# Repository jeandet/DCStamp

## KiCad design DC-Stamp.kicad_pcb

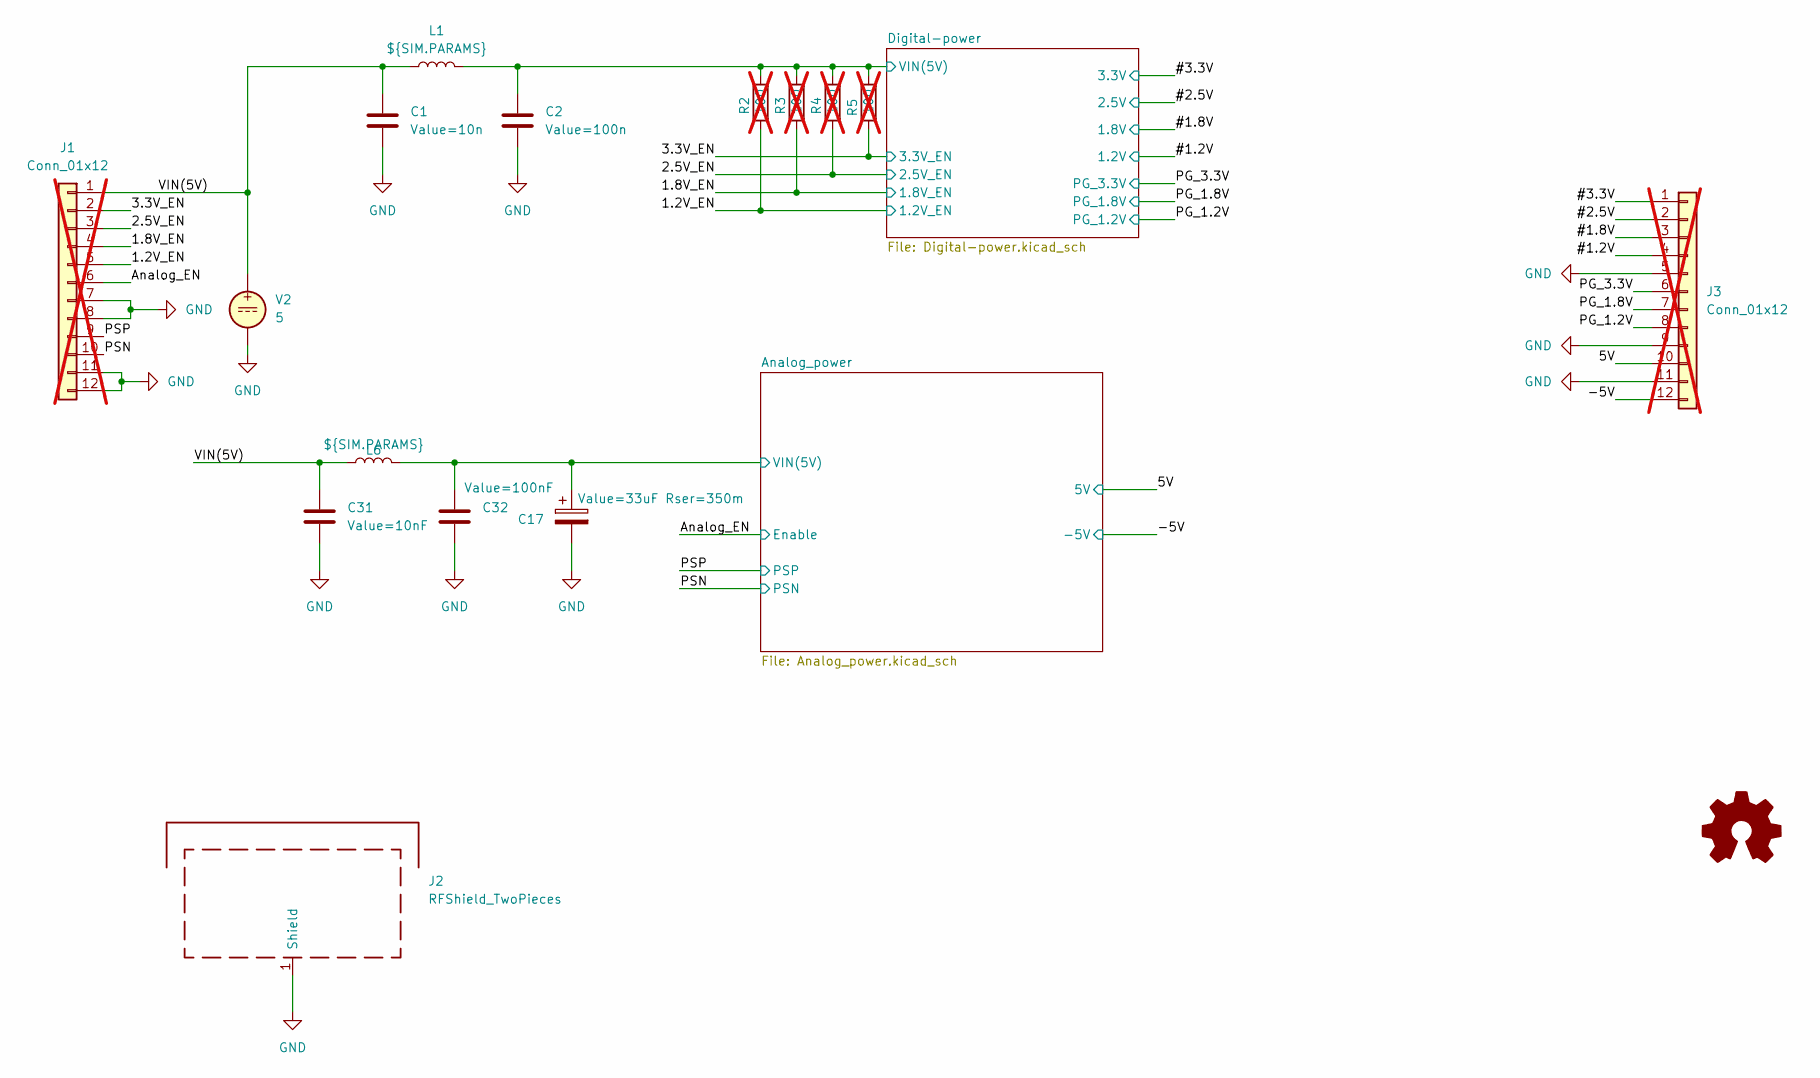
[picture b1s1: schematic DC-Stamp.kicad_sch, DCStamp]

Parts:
C1: Value=10n; C_0603_1608Metric_Pad1.08x0.95mm_HandSolder
C2: Value=100n; C_0603_1608Metric_Pad1.08x0.95mm_HandSolder
C17: Value=33uF Rser=350m; CP_EIA-3528-21_Kemet-B_Pad1.50x2.35mm_HandSolder
C31: Value=10nF; C_0603_1608Metric_Pad1.08x0.95mm_HandSolder
C32: Value=100nF; C_0603_1608Metric_Pad1.08x0.95mm_HandSolder
J1, J3: Conn_01x12; PinHeader_1x12_P2.54mm_Vertical; not fitted
J2: RFShield_TwoPieces; Laird_Technologies_BMI-S-104_32.00x32.00mm
L1, L6: ${SIM.PARAMS}; L_1210_3225Metric_Pad1.42x2.65mm_HandSolder
R2, R3, R4, R5: 100; R_0402_1005Metric_Pad0.72x0.64mm_HandSolder; not fitted
V2: 5
logo1: Logo_Open_Hardware_Small; KiCad-Logo2_5mm_SilkScreen

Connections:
/1.2V_EN: J1.5, R2.2; also elsewhere on the board
/1.8V_EN: J1.4, R3.2; also elsewhere on the board
/2.5V_EN: J1.3, R4.2; also elsewhere on the board
/3.3V_EN: J1.2, R5.2; also elsewhere on the board
/5V: J3.10; also elsewhere on the board
/#1.2V: J3.4; also elsewhere on the board
/#1.8V: J3.3; also elsewhere on the board
/#2.5V: J3.2; also elsewhere on the board
/#3.3V: J3.1; also elsewhere on the board
/-5V: J3.12; also elsewhere on the board
/Analog_EN: J1.6; also elsewhere on the board
/Analog_power/VIN(5V): C17.1, C32.1, L6.2; also elsewhere on the board
/Digital-power/VIN(5V): C2.1, L1.2, R2.1, R3.1, R4.1, R5.1; also elsewhere on the board
/PG_1.2V: J3.8; also elsewhere on the board
/PG_1.8V: J3.7; also elsewhere on the board
/PG_3.3V: J3.6; also elsewhere on the board
/PSN: J1.10; also elsewhere on the board
/PSP: J1.9; also elsewhere on the board
/VIN(5V): C1.1, C31.1, J1.1, L1.1, L6.1, V2.1
GND: C1.2, C2.2, C17.2, C31.2, C32.2, J1.7, J1.8, J1.11, J1.12, J2.1 (Shield), J3.5, J3.9, J3.11, V2.2; also elsewhere on the board

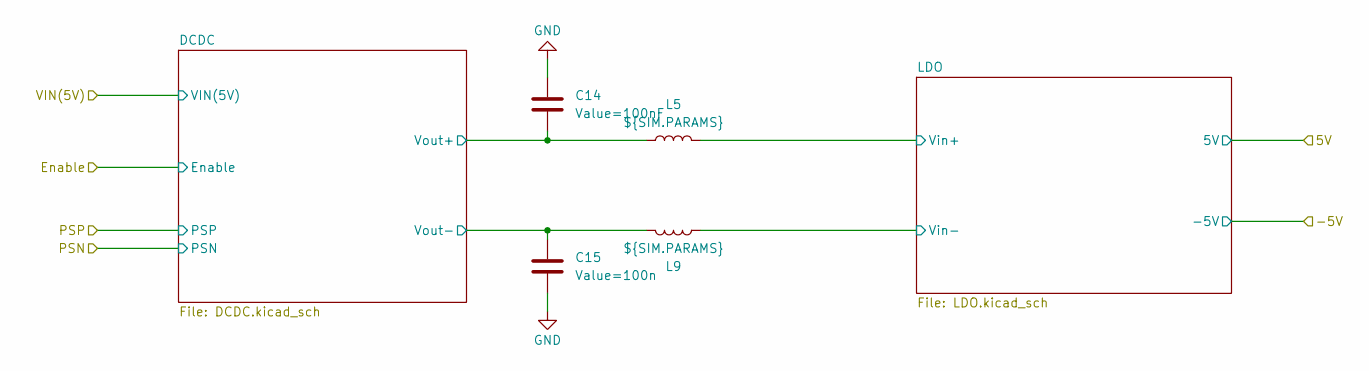
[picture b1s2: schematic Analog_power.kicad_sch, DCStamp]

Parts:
C14: Value=100nF; C_0603_1608Metric_Pad1.08x0.95mm_HandSolder
C15: Value=100n; C_0603_1608Metric_Pad1.08x0.95mm_HandSolder
L5, L9: ${SIM.PARAMS}; L_1210_3225Metric_Pad1.42x2.65mm_HandSolder

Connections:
/Analog_power/DCDC/Vout+: C14.2, L5.1; also elsewhere on the board
/Analog_power/DCDC/Vout-: C15.1, L9.1; also elsewhere on the board
/Analog_power/LDO/Vin+: L5.2; also elsewhere on the board
/Analog_power/LDO/Vin-: L9.2; also elsewhere on the board
GND: C14.1, C15.2; also elsewhere on the board

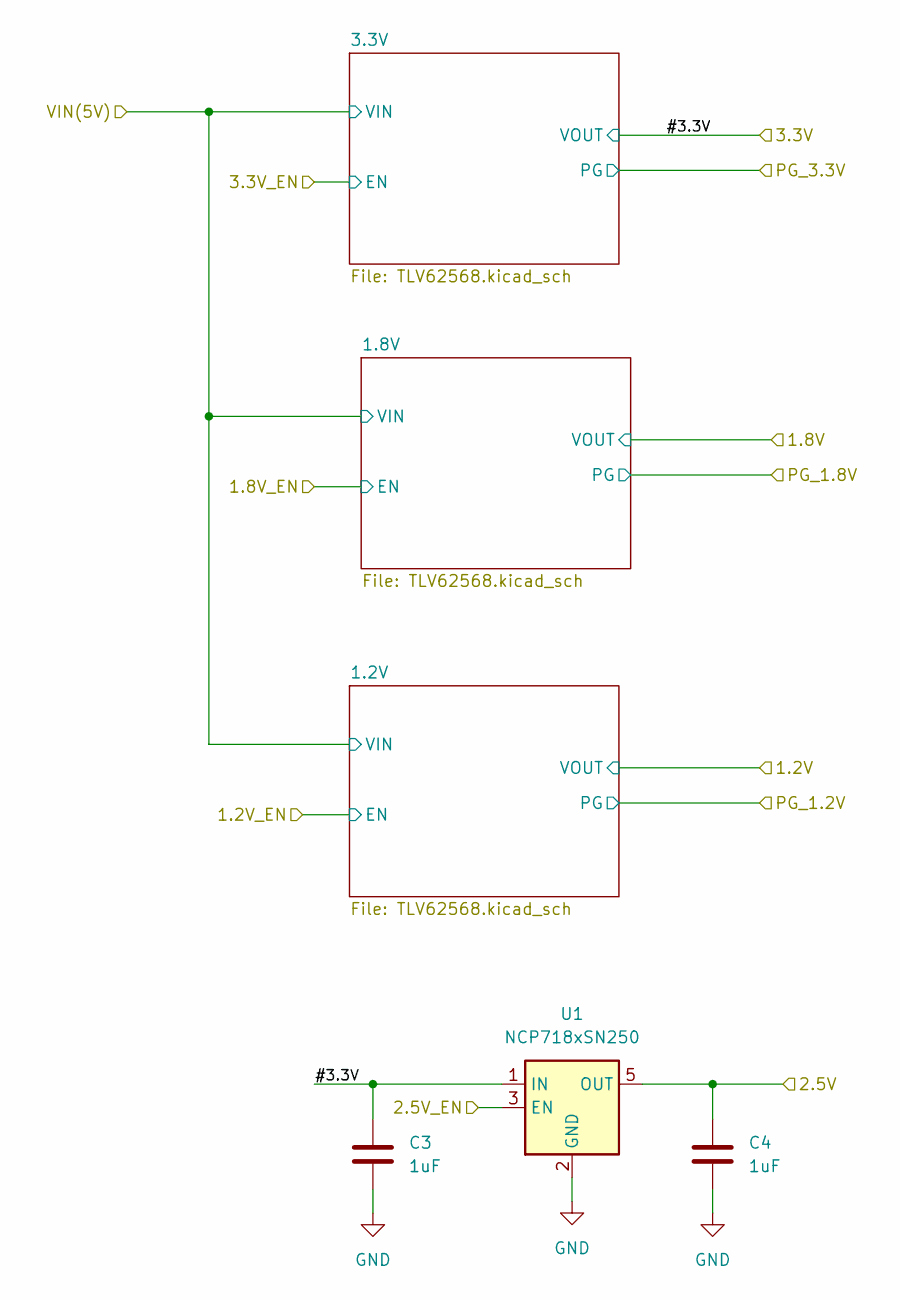
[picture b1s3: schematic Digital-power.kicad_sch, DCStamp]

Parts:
C3, C4: 1uF; C_0603_1608Metric_Pad1.08x0.95mm_HandSolder
U1: NCP718xSN250; SOT-23-5

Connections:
/2.5V_EN: U1.3 (EN); also elsewhere on the board
/#2.5V: C4.1, U1.5 (OUT); also elsewhere on the board
/#3.3V: C3.1, U1.1 (IN); also elsewhere on the board
GND: C3.2, C4.2, U1.2 (GND); also elsewhere on the board

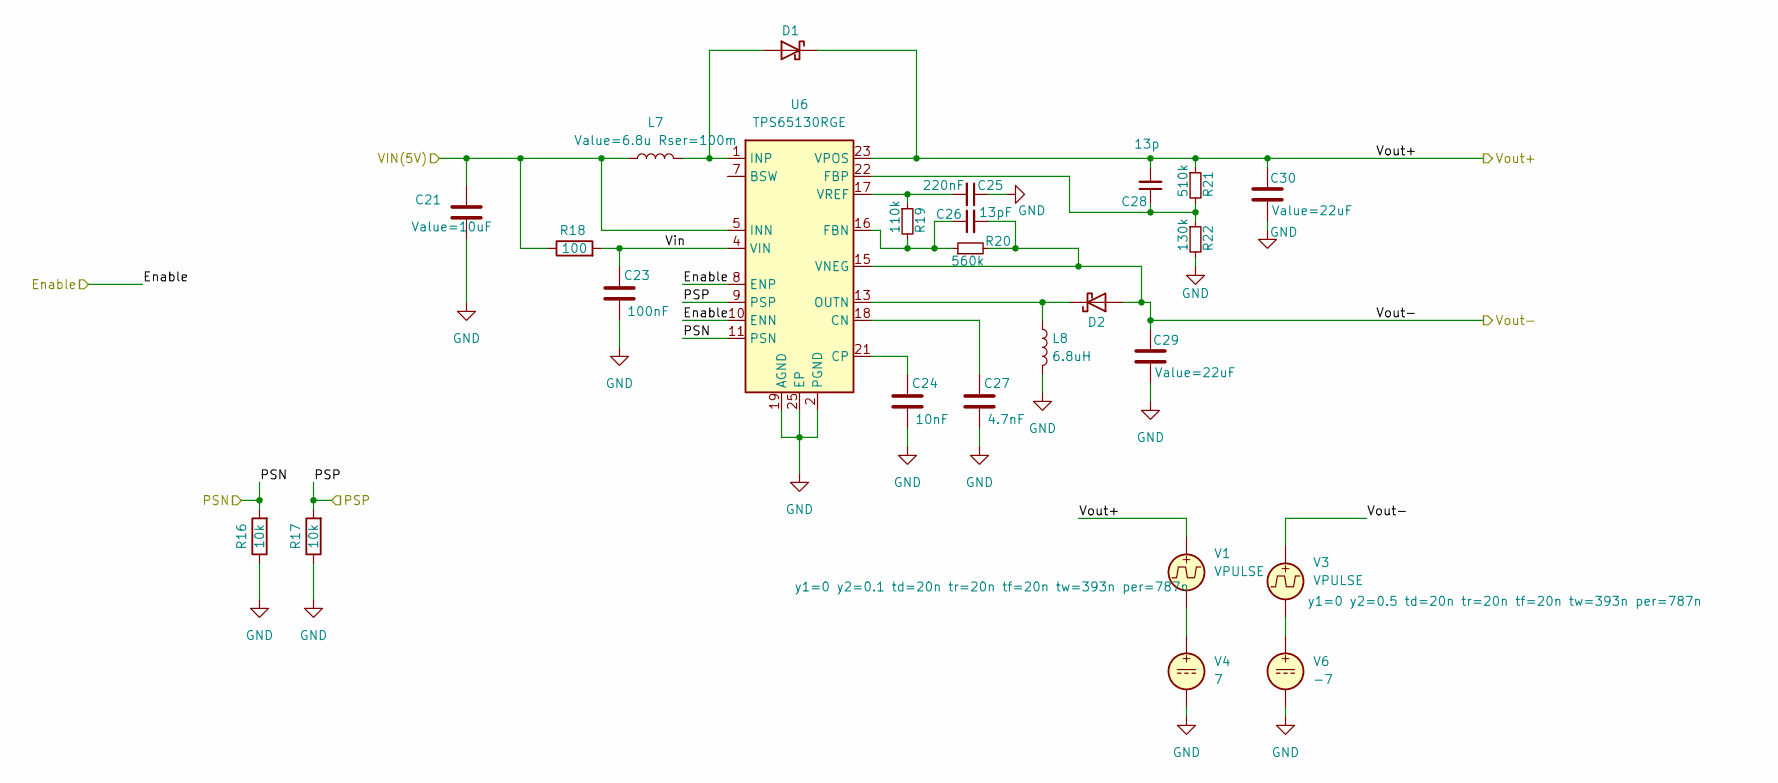
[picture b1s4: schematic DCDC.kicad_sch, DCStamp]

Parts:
C21: Value=10uF; C_1206_3216Metric_Pad1.33x1.80mm_HandSolder
C23: 100nF; C_0402_1005Metric_Pad0.74x0.62mm_HandSolder
C24: 10nF; C_0402_1005Metric_Pad0.74x0.62mm_HandSolder
C25: 220nF; C_0402_1005Metric_Pad0.74x0.62mm_HandSolder
C26: 13pF; C_0402_1005Metric_Pad0.74x0.62mm_HandSolder
C27: 4.7nF; C_0402_1005Metric_Pad0.74x0.62mm_HandSolder
C28: 13p; C_0402_1005Metric_Pad0.74x0.62mm_HandSolder
C29, C30: Value=22uF; C_1206_3216Metric_Pad1.33x1.80mm_HandSolder
D1, D2: D_Schottky; D_Powermite_AK
L7: Value=6.8u Rser=100m; L_Wuerth_WE-TPC-3816
L8: 6.8uH; L_Wuerth_WE-TPC-3816; mouser mouser https://eu.mouser.com/ProductDet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
R16, R17: 10k; R_0402_1005Metric_Pad0.72x0.64mm_HandSolder
R18: 100; R_0402_1005Metric_Pad0.72x0.64mm_HandSolder
R19: 110k; R_0402_1005Metric_Pad0.72x0.64mm_HandSolder
R20: 560k; R_0402_1005Metric_Pad0.72x0.64mm_HandSolder
R21: 510k; R_0402_1005Metric_Pad0.72x0.64mm_HandSolder
R22: 130k; R_0402_1005Metric_Pad0.72x0.64mm_HandSolder
U6: TPS65130RGE; VQFN-24-1EP_4x4mm_P0.5mm_EP2.45x2.45mm_ThermalVias
V1, V3: VPULSE
V4: 7
V6: -7

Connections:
/Analog_EN: U6.8 (ENP), U6.10 (ENN); also elsewhere on the board
/Analog_power/DCDC/Vin: C23.1, R18.2, U6.4 (VIN)
/Analog_power/DCDC/Vout+: C28.2, C30.1, D1.1 (K), R21.1, U6.23 (VPOS); also elsewhere on the board
/Analog_power/DCDC/Vout-: C26.2, C29.1, D2.2 (A), R20.2, U6.15 (VNEG), V3.1; also elsewhere on the board
/Analog_power/VIN(5V): C21.1, L7.1, R18.1, U6.5 (INN), U6.6 (INN); also elsewhere on the board
/PSN: R16.2, U6.11 (PSN); also elsewhere on the board
/PSP: R17.2, U6.9 (PSP); also elsewhere on the board
GND: C21.2, C23.2, C24.2, C25.1, C27.2, C29.2, C30.2, L8.2, R16.1, R17.1, R22.2, U6.2 (PGND), U6.3 (PGND), U6.19 (AGND), U6.25 (EP); also elsewhere on the board
unnamed: D1.2 (A), L7.2, U6.1 (INP), U6.24 (INP)
unnamed: D2.1 (K), L8.1, U6.13 (OUTN), U6.14 (OUTN)
unnamed: C27.1, U6.18 (CN)
unnamed: C24.1, U6.21 (CP)
unnamed: C26.1, R19.2, R20.1, U6.16 (FBN)
unnamed: C28.1, R21.2, R22.1, U6.22 (FBP)
unnamed: C25.2, R19.1, U6.17 (VREF)
unnamed: V1.2, V4.1
unnamed: V3.2, V6.1

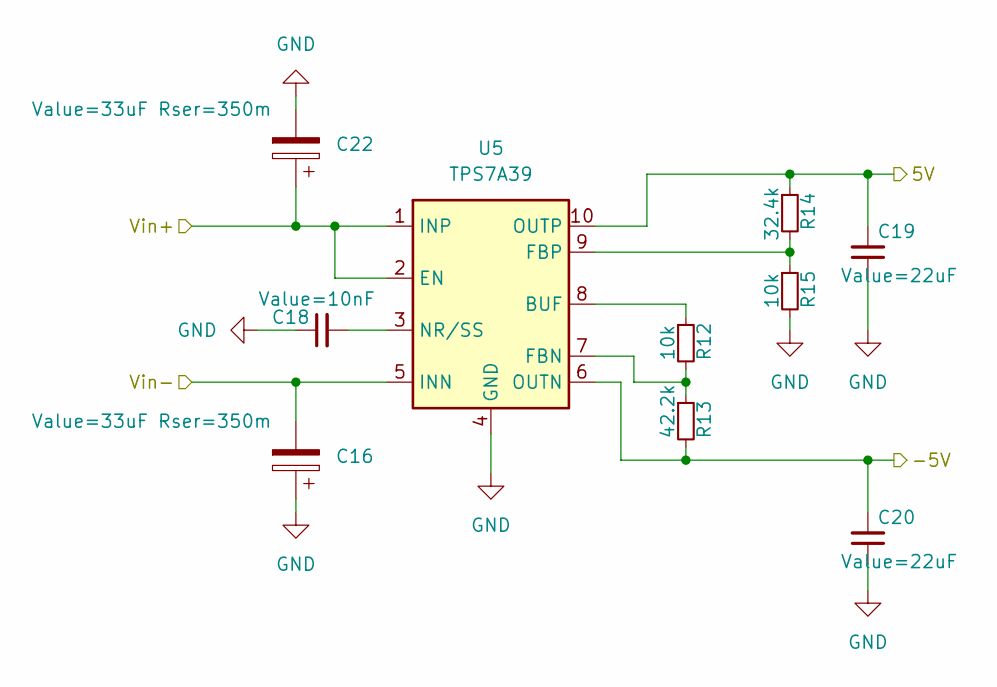
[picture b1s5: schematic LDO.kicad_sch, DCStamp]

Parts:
C16, C22: Value=33uF Rser=350m; CP_EIA-3528-21_Kemet-B_Pad1.50x2.35mm_HandSolder
C18: Value=10nF; C_0603_1608Metric_Pad1.08x0.95mm_HandSolder
C19, C20: Value=22uF; C_1206_3216Metric_Pad1.33x1.80mm_HandSolder
R12, R15: 10k; R_0402_1005Metric_Pad0.72x0.64mm_HandSolder
R13: 42.2k; R_0402_1005Metric_Pad0.72x0.64mm_HandSolder
R14: 32.4k; R_0402_1005Metric_Pad0.72x0.64mm_HandSolder
U5: TPS7A39; Texas_S-PVSON-N10_ThermalVias

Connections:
/5V: C19.2, R14.1, U5.10 (OUTP); also elsewhere on the board
/-5V: C20.2, R13.2, U5.6 (OUTN); also elsewhere on the board
/Analog_power/LDO/Vin+: C22.1, U5.1 (INP), U5.2 (EN); also elsewhere on the board
/Analog_power/LDO/Vin-: C16.2, U5.5 (INN); also elsewhere on the board
GND: C16.1, C18.1, C19.1, C20.1, C22.2, R15.2, U5.4 (GND), U5.11 (GND); also elsewhere on the board
unnamed: R12.1, U5.8 (BUF)
unnamed: R12.2, R13.1, U5.7 (FBN)
unnamed: R14.2, R15.1, U5.9 (FBP)
unnamed: C18.2, U5.3 (NR/SS)

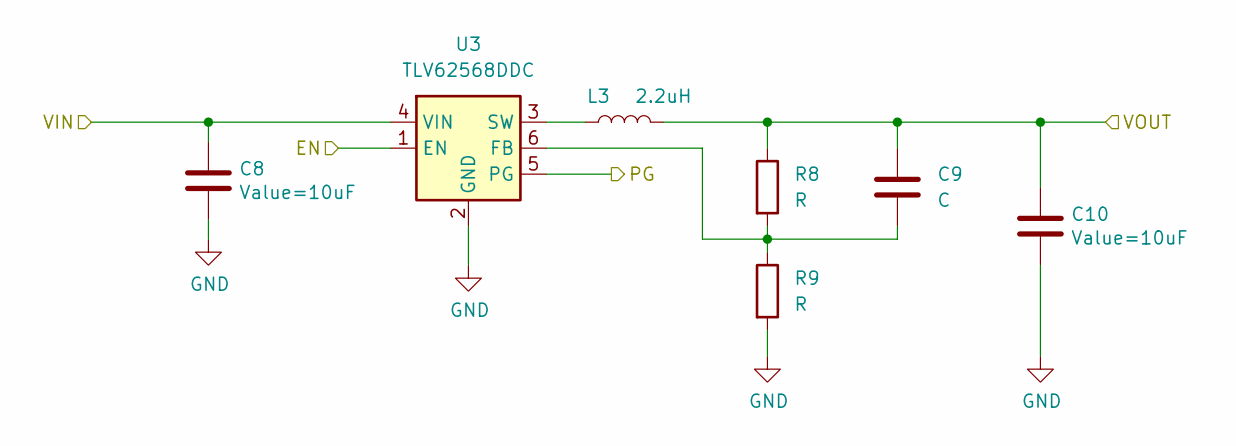
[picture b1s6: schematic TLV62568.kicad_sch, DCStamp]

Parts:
C8, C10: Value=10uF; C_1206_3216Metric_Pad1.33x1.80mm_HandSolder
C9: C; C_0402_1005Metric_Pad0.74x0.62mm_HandSolder
L3: 2.2uH; L_1206_3216Metric_Pad1.42x1.75mm_HandSolder
R8, R9: R; R_0402_1005Metric_Pad0.72x0.64mm_HandSolder
U3: TLV62568DDC; SOT-23-6

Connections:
/1.8V_EN: U3.1 (EN); also elsewhere on the board
/#1.8V: C9.1, C10.1, L3.2, R8.1; also elsewhere on the board
/Digital-power/VIN(5V): C8.1, U3.4 (VIN); also elsewhere on the board
/PG_1.8V: U3.5 (PG); also elsewhere on the board
GND: C8.2, C10.2, R9.2, U3.2 (GND); also elsewhere on the board
unnamed: C9.2, R8.2, R9.1, U3.6 (FB)
unnamed: L3.1, U3.3 (SW)

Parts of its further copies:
C5, C7, C11, C13: Value=10uF; C_1206_3216Metric_Pad1.33x1.80mm_HandSolder
C6, C12: C; C_0402_1005Metric_Pad0.74x0.62mm_HandSolder
L2, L4: 2.2uH; L_1206_3216Metric_Pad1.42x1.75mm_HandSolder
R6, R7, R10, R11: R; R_0402_1005Metric_Pad0.72x0.64mm_HandSolder
U2, U4: TLV62568DDC; SOT-23-6

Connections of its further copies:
/1.2V_EN: U4.1 (EN); also elsewhere on the board
/3.3V_EN: U2.1 (EN); also elsewhere on the board
/#1.2V: C12.1, C13.1, L4.2, R10.1; also elsewhere on the board
/#3.3V: C6.1, C7.1, L2.2, R6.1; also elsewhere on the board
/Digital-power/VIN(5V): C5.1, C11.1, U2.4 (VIN), U4.4 (VIN); also elsewhere on the board
/PG_1.2V: U4.5 (PG); also elsewhere on the board
/PG_3.3V: U2.5 (PG); also elsewhere on the board
GND: C5.2, C7.2, C11.2, C13.2, R7.2, R11.2, U2.2 (GND), U4.2 (GND); also elsewhere on the board
unnamed: C6.2, R6.2, R7.1, U2.6 (FB)
unnamed: L2.1, U2.3 (SW)
unnamed: C12.2, R10.2, R11.1, U4.6 (FB)
unnamed: L4.1, U4.3 (SW)

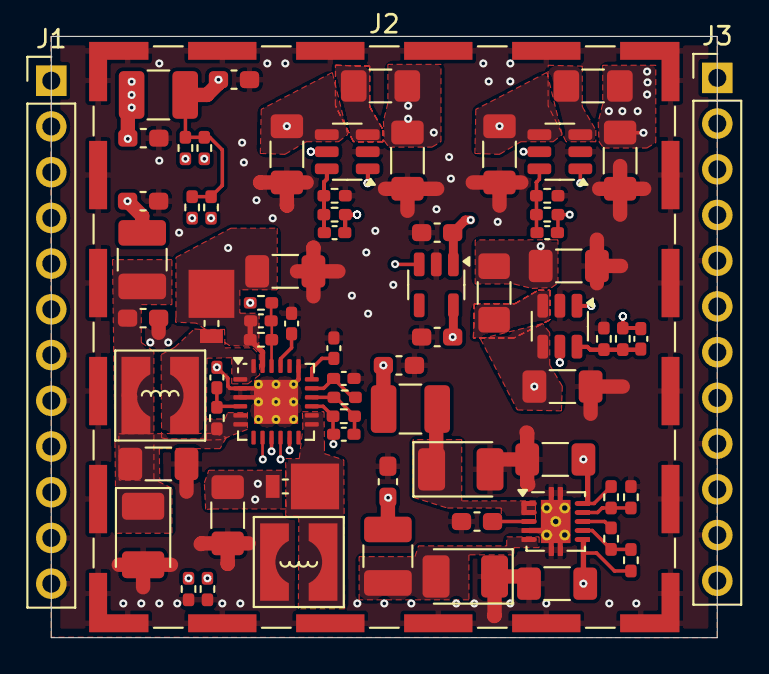
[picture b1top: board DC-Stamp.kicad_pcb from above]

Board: 4 copper layers, 37.0 x 33.4 mm, 74 parts (1 on the bottom side), 42 nets.

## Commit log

2024-09-13 Initial release

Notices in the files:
Analog_power.kicad_sch:
CC-BY-SA
